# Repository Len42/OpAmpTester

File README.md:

# Op Amp Tester

This is a circuit that tests op amp chips to verify that they are working properly. You might find it useful if you repair old equipment, or if your prototype circuits don't always work the way you expect. 🔥😕

### Features

- Tests single, dual, and quad op amp DIP ICs that have the standard pinout
- LEDs blinking = op amps working!
- Powered by a 9-volt battery

### Usage

The circuit board has separate sockets for single, dual, and quad op amp ICs. To test a chip, insert it in the appropriate socket and plug in a 9-volt battery. The LED(s) next to the chip should start blinking. If one or more of the LEDs don't blink, the chip is bad.

### Notes

This tester can test just about any DIP op amp IC (single, dual, or quad) that can operate on a 9 volt power supply and that has the usual pinout. I have tried it with several chips including:
- TL071, TL074
- LM358
- OPA2134

The circuit is designed for a 9-volt power supply. Using a higher supply voltage may not work because the LEDs can't take much reverse voltage.

The PCB layout is provided in KiCad and gerber formats. The PCBs that I used can be ordered from OSH Park. The design is [here.](https://oshpark.com/shared_projects/9kqx3vmx)

I made a [parts list](OpAmpTester-BOM.csv) with links to specific parts and vendors, but most of the components are generic resistors, capacitors, and LEDs - it's not necessary to use the exact parts that I listed. I do recommend using good quality IC sockets because cheap ones are not designed for repeated IC insertion and removal.

Please note that I am a hobbyist, not a trained electronics engineer. No guarantees!

### References

This design is based on some other op amp testers:

- [Edison Science Corner](https://www.youtube.com/watch?v=aGswFkS5oHQ)  
- [NightFire Electronics](https://vakits.com/single-op-amp-tester-kit)  
- [Synthchaser](https://synthchaser.com/product/synthchaser-op-amp-tester/)  

### Software Used

[KiCad](https://www.kicad.org/) 6.0.4

<hr /><div><div style="float:left; padding-right:10px;"></div><div style="xfloat:left; padding-left:10px;"><br />© 2022 Len Popp CC BY<br />This work is licensed under a <a rel="license" href="http://creativecommons.org/licenses/by/4.0/">Creative Commons Attribution 4.0 International License</a>.</div></div>

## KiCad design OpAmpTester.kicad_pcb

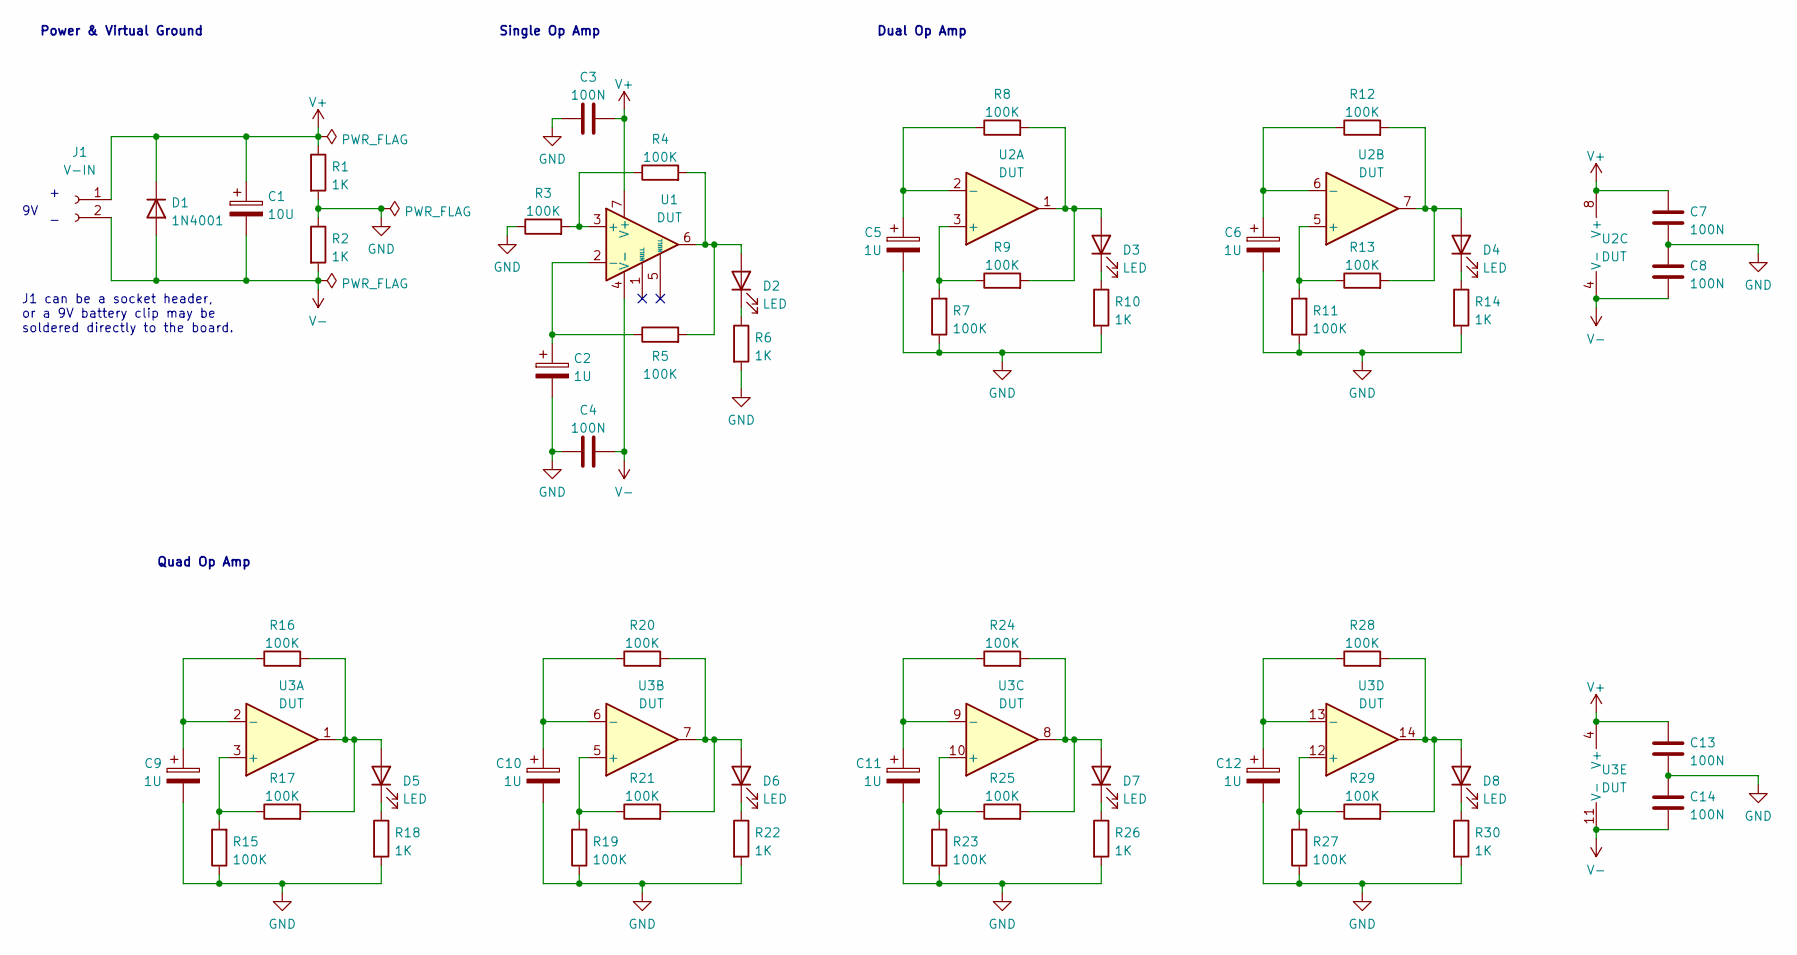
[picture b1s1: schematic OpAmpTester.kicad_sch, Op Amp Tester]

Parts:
C1: 10U; CP_Radial_D5.0mm_P2.50mm; ManufacturerPartNum ECA-1EM100I
C2, C5, C6, C9, C10, C11, C12: 1U; CP_Radial_D4.0mm_P2.50mm; ManufacturerPartNum SEA010M1HBK-0407P
C3, C4, C7, C8, C13, C14: 100N; C_Disc_D5.0mm_W2.5mm_P2.50mm; ManufacturerPartNum FG18X7R1H104KNT06
D1: 1N4001; D_DO-41_SOD81_P10.16mm_Horizontal; ManufacturerPartNum 1N4001RLG
D2, D3, D4, D5, D6, D7, D8: LED; LED_D3.0mm; ManufacturerPartNum LTL-1CHE
J1: V-IN; PinSocket_1x02_P2.54mm_Vertical
R1, R2, R6, R10, R14, R18, R22, R26, R30: 1K; R_Axial_DIN0207_L6.3mm_D2.5mm_P10.16mm_Horizontal; ManufacturerPartNum CCF071K00JKE36
R3, R4, R5, R7, R8, R9, R11, R12, R13, R15, R16, R17, R19, R20, R21, R23, R24, R25, R27, R28, R29: 100K; R_Axial_DIN0207_L6.3mm_D2.5mm_P7.62mm_Horizontal; ManufacturerPartNum MFR-12FTF52-100K
U1, U2: DUT; DIP-8_W7.62mm_Socket; ManufacturerPartNum 110-47-308-41-001000
U3: DUT; DIP-14_W7.62mm_Socket; ManufacturerPartNum 110-47-314-41-001000

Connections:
GND: C2.2, C3.1, C4.1, C5.2, C6.2, C7.2, C8.1, C9.2, C10.2, C11.2, C12.2, C13.2, C14.1, R1.2, R2.1, R3.1, R6.2, R7.1, R10.2, R11.1, R14.2, R15.1, R18.2, R19.1, R22.2, R23.1, R26.2, R27.1, R30.2
unnamed: C2.1, R5.1, U1.2 (-)
unnamed: C5.1, R8.1, U2.2 (-)
unnamed: C6.1, R12.1, U2.6 (-)
unnamed: C9.1, R16.1, U3.2 (-)
unnamed: C10.1, R20.1, U3.6 (-)
unnamed: C11.1, R24.1, U3.9 (-)
unnamed: C12.1, R28.1, U3.13 (-)
unnamed: D2.1 (K), R6.1
unnamed: D2.2 (A), R4.2, R5.2, U1.6
unnamed: D3.1 (K), R10.1
unnamed: D3.2 (A), R8.2, R9.2, U2.1
unnamed: D4.1 (K), R14.1
unnamed: D4.2 (A), R12.2, R13.2, U2.7
unnamed: D5.1 (K), R18.1
unnamed: D5.2 (A), R16.2, R17.2, U3.1
unnamed: D6.1 (K), R22.1
unnamed: D6.2 (A), R20.2, R21.2, U3.7
unnamed: D7.1 (K), R26.1
unnamed: D7.2 (A), R24.2, R25.2, U3.8
unnamed: D8.1 (K), R30.1
unnamed: D8.2 (A), R28.2, R29.2, U3.14
unnamed: R3.2, R4.1, U1.3 (+)
unnamed: R7.2, R9.1, U2.3 (+)
unnamed: R11.2, R13.1, U2.5 (+)
unnamed: R15.2, R17.1, U3.3 (+)
unnamed: R19.2, R21.1, U3.5 (+)
unnamed: R23.2, R25.1, U3.10 (+)
unnamed: R27.2, R29.1, U3.12 (+)
V+: C1.1, C3.2, C7.1, C13.1, D1.1 (K), J1.1, R1.1, U1.7 (V+), U2.8 (V+), U3.4 (V+)
V-: C1.2, C4.2, C8.2, C14.2, D1.2 (A), J1.2, R2.2, U1.4 (V-), U2.4 (V-), U3.11 (V-)

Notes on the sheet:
Single Op Amp
J1 can be a socket header, or a 9V battery clip may be soldered directly to the board.
Dual Op Amp
Quad Op Amp
Power & Virtual Ground

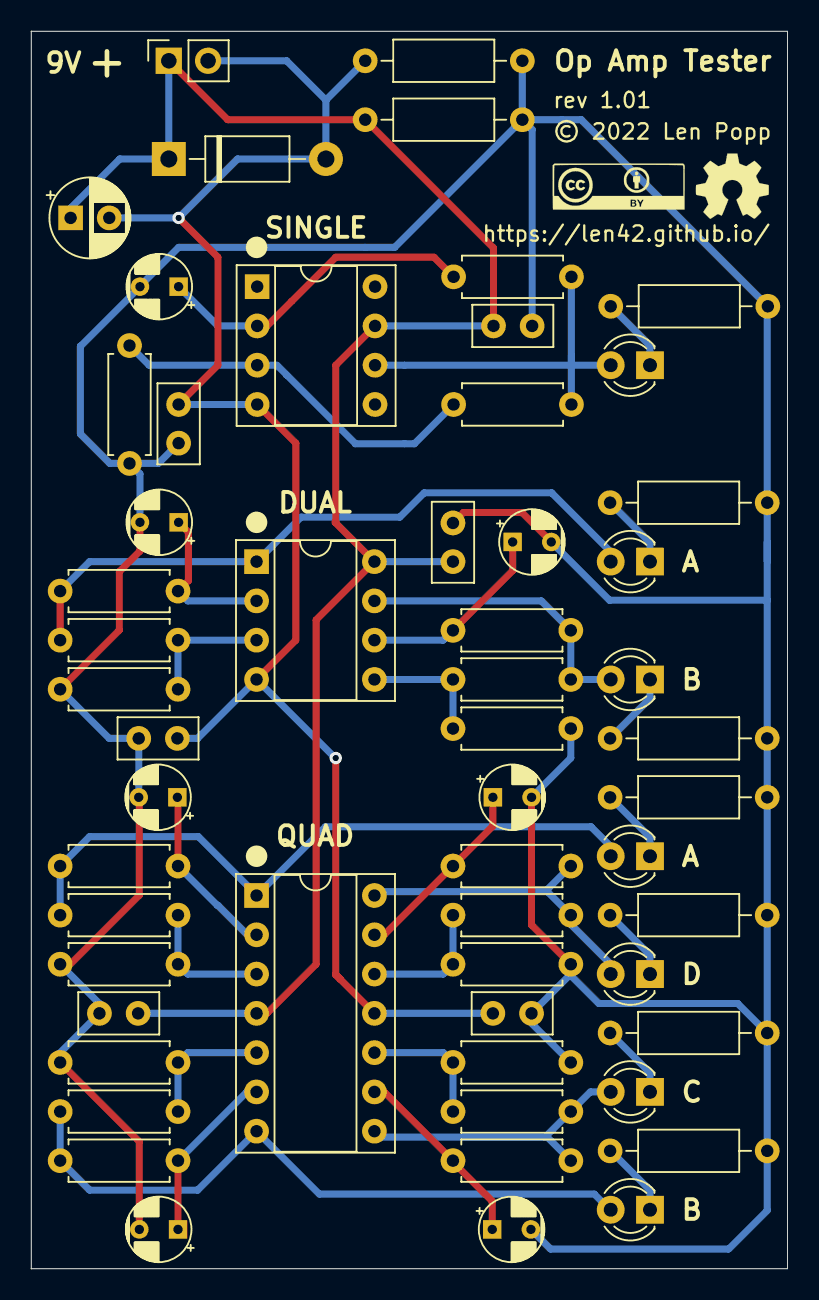
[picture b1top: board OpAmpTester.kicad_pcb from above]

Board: 2 copper layers, 48.9 x 80.0 mm, 56 parts (0 on the bottom side), 31 nets.

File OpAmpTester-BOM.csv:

Ref,Qty,Value,Value2,Note,Description,Datasheet,Manufacturer,ManuPartNum,Distributor1,DistributorPartNum1,DistributorPartLink1,Distributor2,DistributorPartNum2,DistributorPartLink2
"C1","1","10U","","","Capacitor - Electrolytic","https://www.mouser.ca/datasheet/2/315/ABA0000C1218-1131230.pdf","Panasonic","ECA-1EM100I","Mouser","667-ECA-1EM100I","https://www.mouser.ca/ProductDetail/Panasonic/ECA-1EM100I?qs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","","",""
"C2 C5 C6 C9 C10 C11 C12","7","1U","","","Capacitor - Electrolytic","https://www.mouser.ca/datasheet/2/231/161588148197-2307385.pdf","Lelon","SEA010M1HBK-0407P","Mouser","140-SEA1R0M1HBK0407","https://www.mouser.ca/ProductDetail/Lelon/SEA010M1HBK-0407P?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","","",""
"C3 C4 C7 C8 C13 C14","6","100N","","","Capacitor - Ceramic - IC decoupling","https://product.tdk.com/system/files/dam/doc/product/capacit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","TDK","FG18X7R1H104KNT06","Mouser","810-FG18X7R1H104KNT6","https://www.mouser.ca/ProductDetail/810-FG18X7R1H104KNT6","","",""
"D1","1","1N4001","","","50V 1A General Purpose Rectifier Diode, DO-41","http://www.vishay.com/docs/88503/1n4001.pdf","onsemi","1N4001RLG","Mouser","863-1N4001RLG","https://www.mouser.ca/ProductDetail/onsemi/1N4001RLG?qs=y2kk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","","",""
"D2 D3 D4 D5 D6 D7 D8","7","LED","","","Light emitting diode","https://www.mouser.ca/datasheet/2/239/lite-on_lite-s-a000293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","Lite-On","LTL-1CHE","Mouser"," 859-LTL-1CHE","https://www.mouser.ca/ProductDetail/Lite-On/LTL-1CHE?qs=sGAE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","","",""
"J1","1","V-IN","","","Generic connector, single row, 01x02, script generated (kicad-library-utils/schlib/autogen/connector/)","https://cdn-shop.adafruit.com/datasheets/00548.pdf","","","Adafruit","598","https://www.adafruit.com/product/598","Mouser","710-61303211821","https://www.mouser.ca/ProductDetail/Wurth-Elektronik/6130321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"
"R1 R2 R6 R10 R14 R18 R22 R26 R30","9","1K","","","Resistor","https://www.mouser.ca/datasheet/2/427/ccf07-1762725.pdf","Vishay / Dale","CCF071K00JKE36","Mouser","71-CCF071K00JKE36","https://www.mouser.ca/ProductDetail/Vishay-Dale/CCF071K00JKE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","","",""
"R3 R4 R5 R7 R8 R9 R11 R12 R13 R15 R16 R17 R19 R20 R21 R23 R24 R25 R27 R28 R29","21","100K","","","Resistor","https://www.mouser.ca/datasheet/2/447/Yageo_LR_MFR_1-1714151.pdf","YAGEO","MFR-12FTF52-100K","Mouser","603-MFR-12FTF52-100K","https://www.mouser.ca/ProductDetail/YAGEO/MFR-12FTF52-100K?q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","","",""
"U1","1","DUT","","Socket only","Single Low-Noise JFET-Input Operational Amplifiers, DIP-8/SOIC-8","https://www.mouser.ca/datasheet/2/273/MMMC_S_A0004812225_1-2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","Mill-Max","110-47-308-41-001000 ","Mouser","575-1104730841001000","https://www.mouser.ca/ProductDetail/Mill-Max/110-47-308-41-0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","","",""
"U2","1","DUT","","Socket only","Dual Low-Noise JFET-Input Operational Amplifiers, DIP-8/SOIC-8","https://www.mouser.ca/datasheet/2/273/MMMC_S_A0004812225_1-2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","Mill-Max","110-47-308-41-001000 ","Mouser","575-1104730841001000","https://www.mouser.ca/ProductDetail/Mill-Max/110-47-308-41-0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","","",""
"U3","1","DUT","","Socket only","Quad Low-Noise JFET-Input Operational Amplifiers, DIP-14/SOIC-14","https://www.mouser.ca/datasheet/2/273/MMMC_S_A0004813833_1-2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","Mill-Max","110-47-314-41-001000","Mouser","575-1104731441001000","https://www.mouser.ca/ProductDetail/Mill-Max/110-47-314-41-0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","","",""

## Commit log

2022-04-20 Op Amp Tester version 1.0
2022-04-21 add the KiCad page layout file
2022-04-21 BOM file
2022-04-21 schematic tweaks
2022-05-14 update README and photo
2022-05-14 smaller photo
2022-07-06 Add pin-1 indicators for sockets

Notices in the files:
OpAmpTester.kicad_pcb:
Copyright © 2022 Len Popp CC BY
